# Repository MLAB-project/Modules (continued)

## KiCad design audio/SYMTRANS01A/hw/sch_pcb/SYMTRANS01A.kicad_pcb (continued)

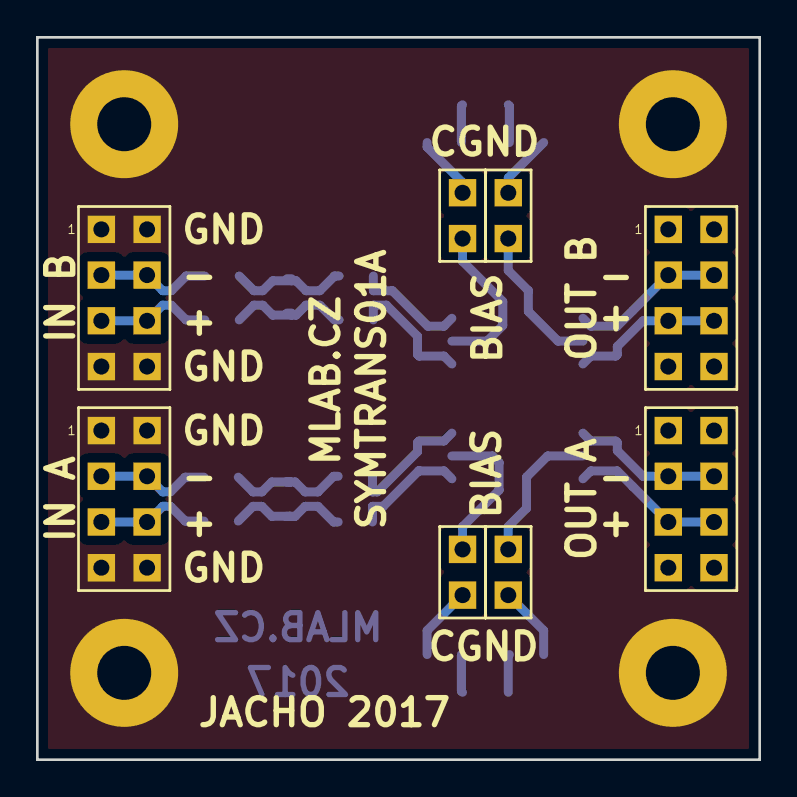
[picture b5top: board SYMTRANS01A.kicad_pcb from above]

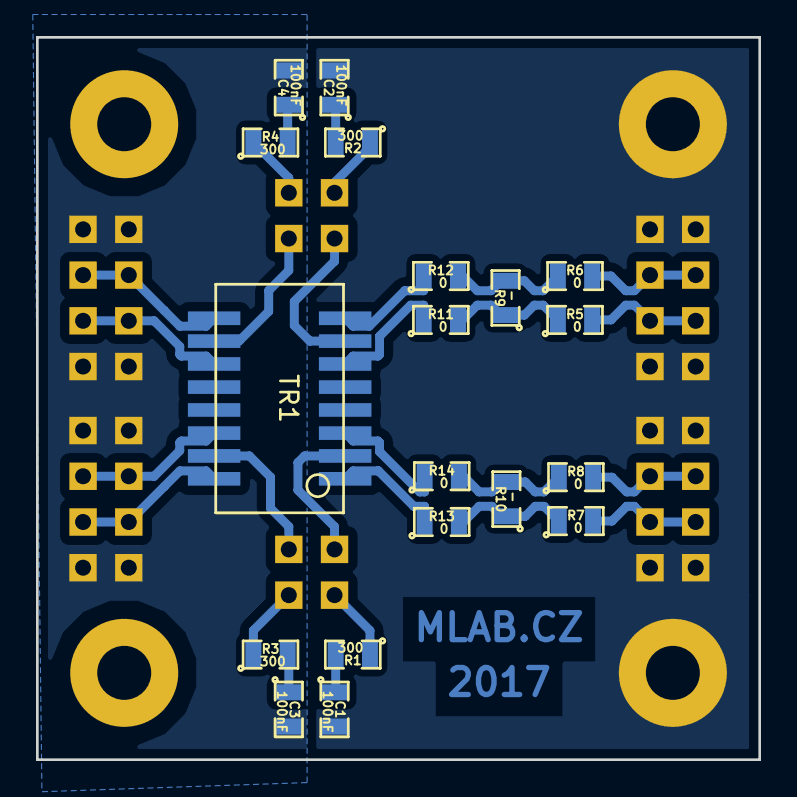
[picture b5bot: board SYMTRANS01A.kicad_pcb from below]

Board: 2 copper layers, 40.1 x 40.1 mm, 31 parts (19 on the bottom side), 30 nets.

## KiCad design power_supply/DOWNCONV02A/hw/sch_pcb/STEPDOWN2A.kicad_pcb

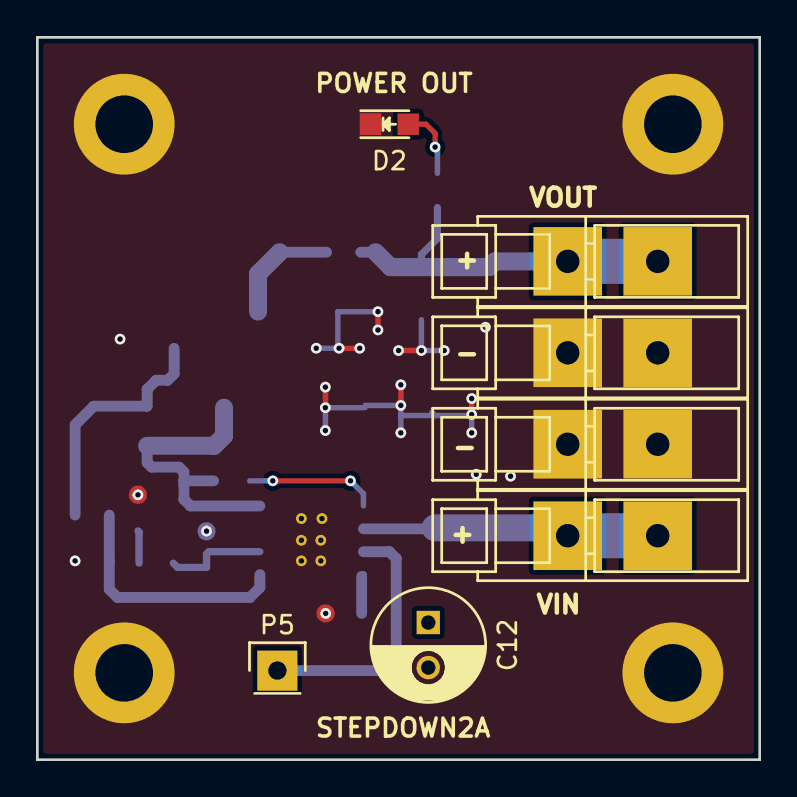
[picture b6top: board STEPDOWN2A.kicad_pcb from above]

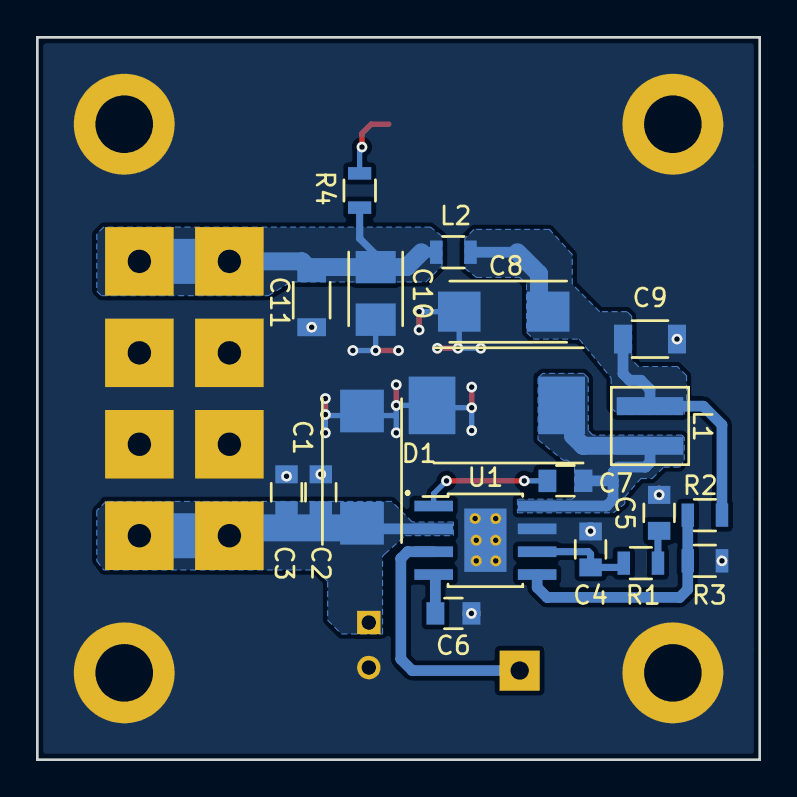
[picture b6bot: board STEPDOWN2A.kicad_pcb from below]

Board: 2 copper layers, 40.1 x 40.1 mm, 30 parts (19 on the bottom side), 12 nets.

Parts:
C1: 22u; TantalC_SizeD_EIA-7343_Reflow
C2: 3u3; C_0805
C3: 1u; C_0805
C4: 18pF; C_0805
C5: 680pF; C_0805
C6: 8n2; C_0805
C7: 100n; C_0805
C8: 22u; TantalC_SizeC_EIA-6032_Reflow
C9, C11: 1u5; C_1206
C10: 22u; TantalC_SizeB_EIA-3528_Reflow
C12: 47u; C_Radial_D6.3_L11.2_P2.5
D1: D_Schottky; DO-214AB
D2: POWER OUT; LED_0805
J1, J2, J3, J4: CONN1_1; WAGO256
L1: 4.7uH; Inductor_XAL4030-472MEB
L2: 240nH; R_0805
P1, P2, P3, P4: _NC; MountingHole_3.2mm_M3_DIN965_Pad
P5: CONN_01X01; Pin_Header_Straight_1x01
R1: 35k7; R_0805
R2: 10k2; R_0805
R3: 1k93; R_0805
R4: 1k2; R_0805
U1: TPS54332; 8-PowerSOIC_Pitch1.27mm

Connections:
+5V: C10.1, C11.1, J3.1, L2.2, R4.1
+12V: C1.1, C2.1, C3.1, C12.1, J1.1, U1.2
/ENABLE: P5.1, U1.3
GND: C1.2, C2.2, C3.2, C4.2, C5.2, C6.2, C8.2, C9.2, C10.2, C11.2, C12.2, D1.2, D2.1, J2.1, J4.1, P1.1, P2.1, P3.1, P4.1, R3.2, U1.7, U1.9
unnamed: C4.1, R1.1, U1.6
unnamed: C5.1, R1.2
unnamed: C6.1, U1.4
unnamed: C7.1, D1.1, L1.1, U1.8
unnamed: C7.2, U1.1
unnamed: C8.1, C9.1, L1.2, L2.1, R2.1
unnamed: D2.2, R4.2
unnamed: R2.2, R3.1, U1.5

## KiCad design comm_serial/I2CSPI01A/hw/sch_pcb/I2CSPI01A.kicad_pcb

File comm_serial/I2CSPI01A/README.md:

[Czech](./README.cs.md)
<!--- module --->
# I2CSPI01A
<!--- Emodule --->

<!--- subtitle --->I2C to SPI bridge<!--- Esubtitle --->

<!--- description --->Allows connection of SPI devices to I2C bus. The module is capable co handle up to four SPI slaves. Not used chip-select pins can be used as GPIO pins.<!--- Edescription --->

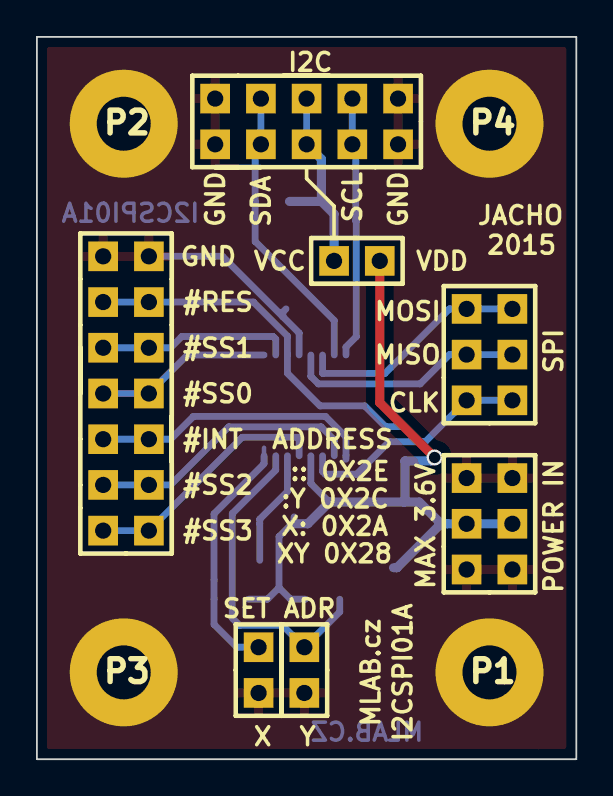
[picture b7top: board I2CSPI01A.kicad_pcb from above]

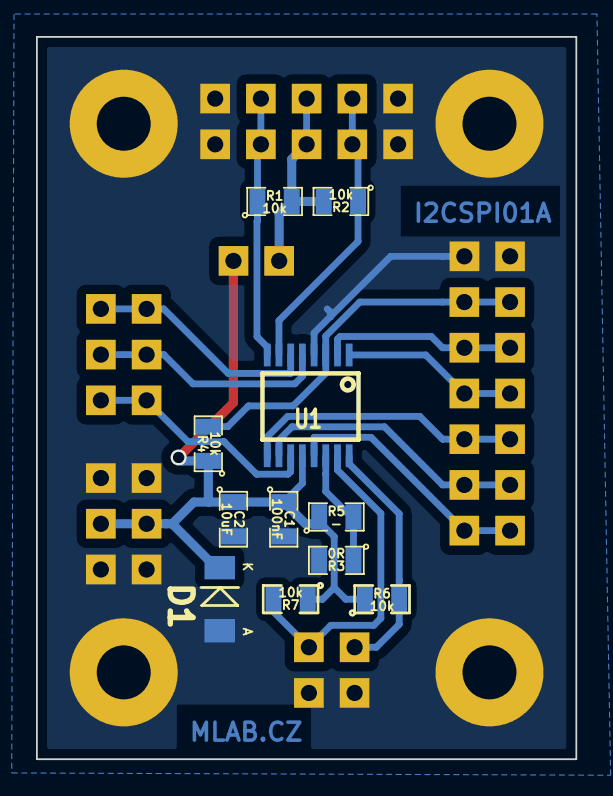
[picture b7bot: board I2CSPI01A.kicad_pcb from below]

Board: 2 copper layers, 30.0 x 40.1 mm, 22 parts (11 on the bottom side), 17 nets.

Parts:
C1: 100nF; SMD-0805
C2: 10uF; SMD-0805
D1: BZV55C-3,6V; Diode-MiniMELF_Standard
J1, J4: JUMP_3X2; Pin_Header_Straight_2x03
J2: JUMP_5X2; Pin_Header_Straight_2x05
J3: JUMP_7X2; Pin_Header_Straight_2x07
J5, J6, J7: CONN_2; Pin_Header_Straight_1x02
P1, P2, P3, P4: _; MountingHole_3mm
R1, R2, R4, R6, R7: 10k; SMD-0805
R3: 0R; SMD-0805
R5: -; SMD-0805
U1: SC18IS602B; TSSOP-16

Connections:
/#INT: J3.3, J3.12, U1.9
/#RES: J3.6, J3.9, R4.2, U1.3
/#SS0: J3.4, J3.11, U1.1
/#SS1: J3.5, J3.10, U1.2
/#SS2: J3.2, J3.13, U1.10
/#SS3: J3.1, J3.14, U1.13
/A0: R3.1, R5.2, U1.14
/A1: J7.2, R7.2, U1.15
/A2: J6.1, R6.2, U1.16
/MISO: J1.2, J1.5, U1.5
/MOSI: J1.3, J1.4, U1.6
/SCL: J2.2, J2.9, R1.1, U1.8
/SDA: J2.4, J2.7, R2.1, U1.7
/SPICLK: J1.1, J1.6, U1.11
GND: C1.2, C2.2, D1.1, J2.1, J2.5, J2.6, J2.10, J3.7, J3.8, J4.1, J4.3, J4.4, J4.6, J6.2, J7.1, P1.1, P2.1, P3.1, P4.1, R3.2, U1.4
unnamed: J2.3, J2.8, J5.1, R1.2, R2.2
VDD: C1.1, C2.1, D1.2, J4.2, J4.5, J5.2, R4.1, R5.1, R6.1, R7.1, U1.12

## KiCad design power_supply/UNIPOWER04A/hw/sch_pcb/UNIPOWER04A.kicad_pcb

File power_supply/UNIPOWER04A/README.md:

[Czech](./README.cs.md)
<!--- module --->
# UNIPOWER04A
<!--- Emodule --->

<!--- subtitle --->UNIPOWER04A <!--- Esubtitle --->

<!--- description ---> Universal 10x 1A power supply module 5V or 12V.<!--- Edescription --->

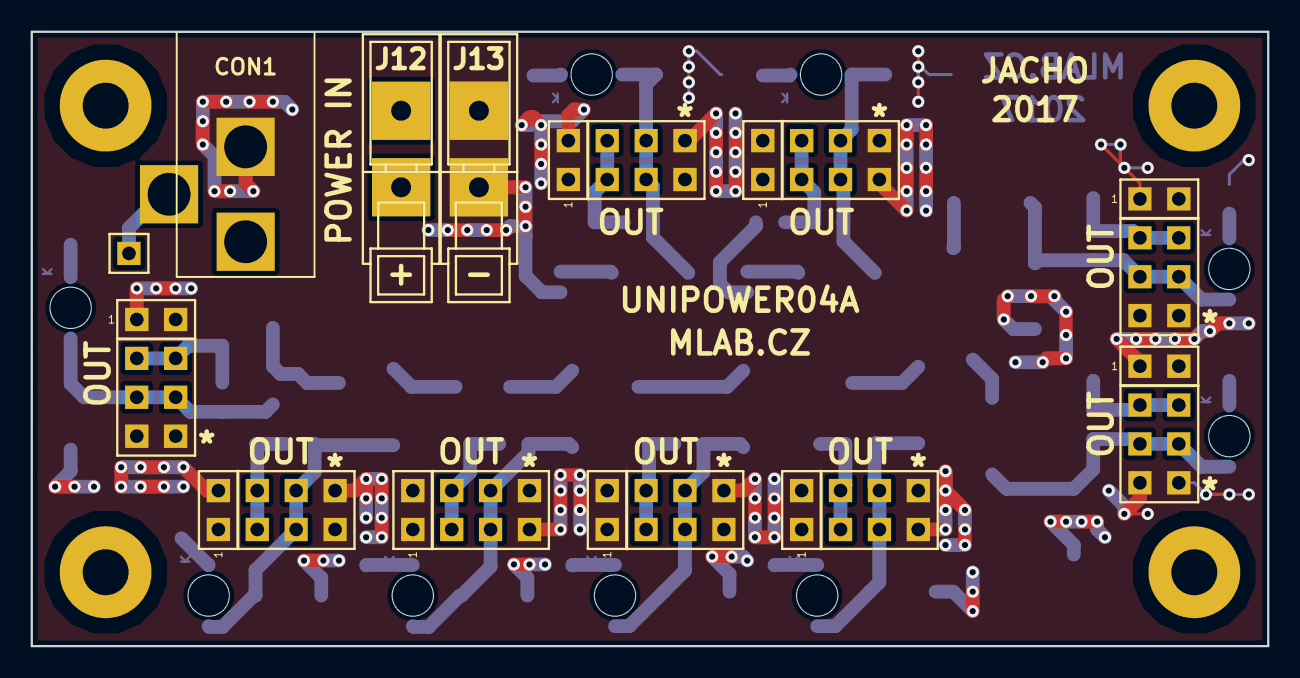
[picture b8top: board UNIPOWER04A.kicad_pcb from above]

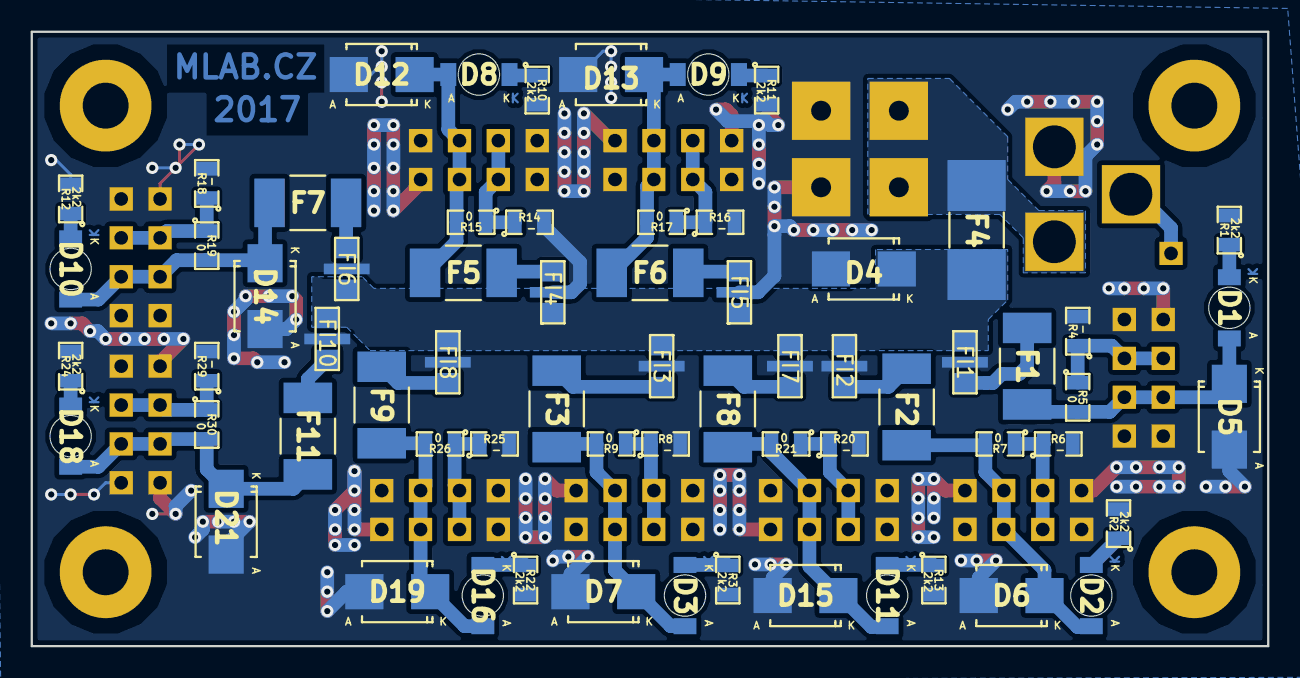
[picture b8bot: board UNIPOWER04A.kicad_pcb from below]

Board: 2 copper layers, 80.8 x 40.1 mm, 82 parts (65 on the bottom side), 40 nets.

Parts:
CON1: JACK_DC2.1; DC2,1MM
D1, D2, D3, D8, D9, D10, D11, D16, D18: RED; LED_1206
D4, D5, D6, D7, D12, D13, D14, D15, D19, D21: SMBJ15A-E3/52; SMB_Standard
F1, F2, F3, F5, F6, F7, F8, F9, F11: 1,1A; 2410
F4: 10A; Drzak_2410
FI1, FI2, FI3, FI4, FI5, FI6, FI7, FI8, FI10: NFM21PC105; FIR1
J1: CONN1_1; Straight_1x01
J2, J3, J4, J5, J6, J7, J8, J9, J11: JUMP_4X2; Straight_2x04
J12, J13: CONN1_1; WAGO256
P1, P2, P3, P4: _; MountingHole_3mm
R1, R2, R3, R10, R11, R12, R13, R22, R24: 2k2; SMD-0805
R4, R6, R8, R14, R16, R18, R20, R25, R29: -; SMD-0805
R5, R7, R9, R15, R17, R19, R21, R26, R30: 0; SMD-0805

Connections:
GND: CON1.2, D4.2, D5.2, D6.2, D7.2, D12.2, D13.2, D14.2, D15.2, D19.2, D21.2, FI1.2, FI2.2, FI3.2, FI4.2, FI5.2, FI6.2, FI7.2, FI8.2, FI10.2, J2.1, J2.2, J2.7, J2.8, J3.1, J3.2, J3.7, J3.8, J4.1, J4.2, J4.7, J4.8, J5.1, J5.2, J5.7, J5.8, J6.1, J6.2, J6.7, J6.8, J7.1, J7.2, J7.7, J7.8, J8.1, J8.2, J8.7, J8.8, J9.1, J9.2, J9.7, J9.8, J11.1, J11.2, J11.7, J11.8, J13.1, R1.2, R2.2, R3.2, R4.2, R6.2, R8.2, R10.2, R11.2, R12.2, R13.2, R14.2, R16.2, R18.2, R20.2, R22.2, R24.2, R25.2, R29.2
unnamed: CON1.1, F4.1, J12.1
unnamed: CON1.3, J1.1
unnamed: D1.1, R1.1
unnamed: D1.2, D5.1, F1.2, J2.5, J2.6, R5.2
unnamed: D2.1, R2.1
unnamed: D2.2, D6.1, F2.2, J3.5, J3.6, R7.2
unnamed: D3.1, R3.1
unnamed: D3.2, D7.1, F3.2, J4.5, J4.6, R9.2
unnamed: D8.1, R10.1
unnamed: D9.1, R11.1
unnamed: D10.1, R12.1
unnamed: D10.2, D14.1, F7.2, J7.5, J7.6, R19.2
unnamed: D11.1, R13.1
unnamed: D11.2, D15.1, F8.2, J8.5, J8.6, R21.2
unnamed: D8.2, D12.1, F5.2, J5.5, J5.6, R15.2
unnamed: D9.2, D13.1, F6.2, J6.5, J6.6, R17.2
unnamed: D16.1, R22.1
unnamed: D16.2, D19.1, F9.2, J9.5, J9.6, R26.2
unnamed: D18.1, R24.1
unnamed: D18.2, D21.1, F11.2, J11.5, J11.6, R30.2
unnamed: F1.1, FI1.3
unnamed: F2.1, FI2.3
unnamed: F3.1, FI3.3
unnamed: F5.1, FI4.3
unnamed: F6.1, FI5.3
unnamed: F7.1, FI6.3
unnamed: F8.1, FI7.3
unnamed: F9.1, FI8.3
unnamed: F11.1, FI10.3
unnamed: J2.3, J2.4, R4.1, R5.1
unnamed: J3.3, J3.4, R6.1, R7.1
unnamed: J4.3, J4.4, R8.1, R9.1
unnamed: J5.3, J5.4, R14.1, R15.1
unnamed: J6.3, J6.4, R16.1, R17.1
unnamed: J7.3, J7.4, R18.1, R19.1
unnamed: J8.3, J8.4, R20.1, R21.1
unnamed: J9.3, J9.4, R25.1, R26.1
unnamed: J11.3, J11.4, R29.1, R30.1
VCC: D4.1, F4.2, FI1.1, FI2.1, FI3.1, FI4.1, FI5.1, FI6.1, FI7.1, FI8.1, FI10.1

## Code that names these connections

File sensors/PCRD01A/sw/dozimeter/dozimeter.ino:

/* PCRD */

/*
 * SD card attached to SPI bus as follows:
 ** SDcard01B/CMD      MOSI - pin PB3
 ** SDcard01B/DATA0    MISO - pin PB4
 ** SDcard01B/CLK      CLK  - pin PB5
 ** SDcard01B/CD/DATA3 CS   - pin PD4
*/

#include <SD.h>

const String filename = "log.csv";  // filename for logfile

const int detector=3; // PD3
const int eint=2;     // PD2
const int LED1=8;     // PB0
const int LED2=9;     // PB1
const int LED3=10;    // PB2
const int LED4=7;     // PD7
const int chipSelect = 4;     // CS is PD4

const int CHANNELS=64;  // Number of channels

unsigned int channel[CHANNELS];    // recordig buffer
int interval=0;               // seconds counter
boolean rise=false;           // flag fo recording time
char inChar;                  // input character from GPS
String dataString = "";       // concantenated string with NMEA messages and measured values
int coll = 0;                 // collons counter in NMEA messages
unsigned int i = 0;           // measurements counter


// function for reading $GPRMC NMEA message
void ReadGPRMC()
{
  // $GPRMC,091451.00,A,4915.64143,N,01441.50397,E,0.053,,090215,,,A*74
  coll = 0;
  while(1)    // wait for $GPRMC
  {
    // get incoming byte:
    while (!Serial.available());
    if (Serial.read() != '$') continue;
    while (!Serial.available());
    if (Serial.read() != 'G') continue;
    while (!Serial.available());
    if (Serial.read() != 'P') continue;
    while (!Serial.available());
    if (Serial.read() != 'R') continue;
    while (!Serial.available());
    if (Serial.read() != 'M') continue;
    while (!Serial.available());
    if (Serial.read() != 'C') continue;
    while (!Serial.available());
    if (Serial.read() != ',') continue;
    break;
  }  
  do
  {
    while (!Serial.available());
    inChar = (char)Serial.read();
    if (inChar == ',') coll++;
    dataString += inChar;
  }
  while (coll < 9);  // read only 9 coma separated values
}

// function for reading $GPGGA NMEA message
void ReadGPGGA()
{
  // $GPGGA,091451.00,4915.64143,N,01441.50397,E,1,09,0.90,443.2,M,44.0,M,,*50
  coll = 0;
  while(1)  // wait for $GPGGA
  {
    while (!Serial.available());
    if (Serial.read() != '$') continue;
    while (!Serial.available());
    if (Serial.read() != 'G') continue;
    while (!Serial.available());
    if (Serial.read() != 'P') continue;
    while (!Serial.available());
    if (Serial.read() != 'G') continue;
    while (!Serial.available());
    if (Serial.read() != 'G') continue;
    while (!Serial.available());
    if (Serial.read() != 'A') continue;
    while (!Serial.available());
    if (Serial.read() != ',') continue;
    break;
  }  
  do
  {
    while (!Serial.available());
    inChar = (char)Serial.read();
    if (inChar == ',') coll++;
    if (coll > 4) dataString += inChar;  // skip first 5 coma separated values
  }
  while (coll < 12); // read only 7 coma separated values
}

void isr()        // interrupt service routine driven from 1PPS from GPS
{
  if (++interval == 10) // 10 seconds
  {
    rise=true;
    interval = 0;
  }

}

void record()
{
  for (int c=16; c<CHANNELS; c++)
  {
    if (channel[c]>0)
    {
      digitalWrite(LED4, HIGH);   // LED 16-64
      break;      
    }
  }

  for (int c=9; c<17; c++)
  {
    if (channel[c]>0)
    {
      digitalWrite(LED3, HIGH);   // LED 9-16
      break;      
    }
  }

  for (int c=5; c<9; c++)
  {
    if (channel[c]>0)
    {
      digitalWrite(LED2, HIGH);   // LED 5-8
      break;      
    }
  }

  for (int c=0; c<5; c++)
  {
    if (channel[c]>0)
    {
      digitalWrite(LED1, HIGH);   // LED 0-4
      break;      
    }
  }
     
  dataString = "";        // make a string for assembling the data to log
  ReadGPRMC();            // read NMEA sentences from GPS
  ReadGPGGA();
  // make a string for assembling the data to log:
  dataString += String(i++);
  //dataString += ","; 
  //Serial.print(dataString);

  for (int n=0; n<CHANNELS; n++)
  {
    dataString += ","; 
    dataString += String(channel[n]);
    //Serial.print(channel[n]);
    //Serial.print(',');
  }
  //Serial.println();
  
  // open the file. note that only one file can be open at a time,
  // so you have to close this one before opening another.
  char fileNameCharArray[filename.length()];
  filename.toCharArray(fileNameCharArray, filename.length());
  File dataFile = SD.open(fileNameCharArray, FILE_WRITE);

  // if the file is available, write to it:
  if (dataFile) 
  {
    dataFile.println(dataString);
    dataFile.close();
    // print to the serial port too:
    Serial.println(dataString);
  }  
  // if the file isn't open, pop up an error:
  else {
    Serial.println("error opening datalog.CSV");
  } 

  for (int n=0; n<CHANNELS; n++) // clear recording buffer
  {
    channel[n]=0;
  }  

  digitalWrite(LED1, LOW);   // LED OFF
  digitalWrite(LED2, LOW);   // LED OFF
  digitalWrite(LED3, LOW);   // LED OFF
  digitalWrite(LED4, LOW);   // LED OFF

}

void setup() 
{
 // Open serial communications and wait for port to open:
  Serial.begin(9600);
  while (!Serial) {;}
  Serial.println("cvak");

  pinMode(detector, INPUT);
  pinMode(eint, INPUT);
  pinMode(LED1, OUTPUT);
  pinMode(LED2, OUTPUT);
  pinMode(LED3, OUTPUT);
  pinMode(LED4, OUTPUT);


  Serial.print("Initializing SD card...");  // inserting a SD Card always reset the processor and call setup
  // make sure that the default chip select pin is set to
  // output, even if you don't use it:
  //pinMode(10, OUTPUT); // PB2
  //pinMode(LED, OUTPUT);     

  // see if the card is present and can be initialized:
  if (!SD.begin(chipSelect)) 
  {
    Serial.println("Card failed, or not present");
    // don't do anything more:
    return;
  }
  Serial.println("card initialized.");

  noInterrupts();          // disable all interrupts
  attachInterrupt(0, isr, RISING);  // initialise interrupt from rising edge of 1PPS

  for (int n=0; n<CHANNELS; n++) // clear recoding buffer
  {
    channel[n]=0; 
  }

  interrupts();             // enable all interrupts
  
  Serial.println("Hmmm");
}

void loop() 
{
  while (true)
  {
    unsigned int duration=0;               // pulse duration counter
  
    while (!digitalRead(detector))  // waiting for pulse
    {
      if (rise) break;
    }
    while (digitalRead(detector)) 
    {
      if (rise) break;
      if (duration < (CHANNELS-1)) duration++;
    }
    if (rise)  // recording time is now
    {
        record();  // make record
        rise = false;
        continue;  // skip this interrupted impuls
    }
    if (channel[duration] < 65535) channel[duration]++;  /// record duration in apropriate channel
  }
}

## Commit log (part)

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2022-02-16 [MLABweb] Documentation edits; TRIMQUAD01A
2022-02-16 [MLABweb] Documentation edits; LEDbar01A
2022-02-16 [MLABweb] Documentation edits; SDcard01A
2022-02-16 [MLABweb] Documentation edits; PIC16F87xTQ4401A
2022-02-16 [MLABweb] Documentation edits; PICICD01B
2022-02-16 [MLABweb] Documentation edits; Galileo
2022-02-16 [MLABweb] Documentation edits; ATmega8DIL01A
2022-02-16 [MLABweb] Documentation edits; AVRUSB01A
2022-02-16 [MLABweb] Documentation edits; ATmegaTQ10001A
2022-02-16 [MLABweb] Documentation edits; RFM02SMD01A
2022-02-16 [MLABweb] Documentation edits; BP01A
2022-02-16 [MLABweb] Documentation edits; PCRD01A
2022-02-16 [MLABweb] Documentation edits; S3AN01B
2022-02-16 [MLABweb] Documentation edits; LDD01A
2022-02-16 [MLABweb] Documentation edits; SMA2SATA01A
2022-02-16 [MLABweb] Documentation edits; HBRIDGE02A
2022-02-16 [MLABweb] Documentation edits; HBRIDGE01B
2022-02-16 [MLABweb] Documentation edits; MPC17511HB01A
2022-02-16 [MLABweb] Documentation edits; S3AN01A
2022-02-16 [MLABweb] Documentation edits; OZquad01A
2022-02-16 [MLABweb] Documentation edits; POWERDAC01A
2022-02-16 [MLABweb] Documentation edits; MBA81001A
2022-02-16 [MLABweb] Documentation edits; NFET2X01A
2022-02-16 [MLABweb] Documentation edits; PWMLED01A
2022-02-16 [MLABweb] Documentation edits; CLKGEN01A
2022-02-16 [MLABweb] Documentation edits; USB232R01A
2022-02-16 [MLABweb] Documentation edits; I2CHUB01B
2022-02-16 [MLABweb] Documentation edits; ETH01A
2022-02-16 [MLABweb] Documentation edits; SUPERCAP01A
2022-02-16 [MLABweb] Documentation edits; LION2CELL01C
2022-02-16 [MLABweb] Documentation edits; BATPOWER02A
2022-02-16 [MLABweb] Documentation edits; GPS02A
2022-02-17 [MLABweb] Documentation edits; CLKHUB01A
2022-02-17 Module moved to separate repository https://github.com/mlab-modules/ADCoctoSPI01
2022-02-17 Update submodule.
2022-02-18 Remove redundant files to submodules from the repository.
2022-03-08 TTLLVDS01A moved to separate submodule. https://github.com/mlab-modules/TTLLVDS01
2022-04-03 Add links to datasheets.
2022-04-03 Adding submodule STEPUPDC01A
2022-04-05 Adding USBI2C01A as submodule.
2022-04-05 Adding I2CHUB02 as submodule.
2022-08-14 Moving VCAI2C01 to separate repository. https://github.com/mlab-modules/VCAI2C01
2022-08-14 adding submodules of separate repositories.
2023-02-07 Removing ACOMP01A module. Will be designed from ground in the new repository.
2023-04-01 Removing ADC modules splitted to separate repositories.
2023-05-08 Removing ALBASE modules splitted to separate repositories.
2023-05-08 update split script
2023-05-08 Removing ALBASE1609 modules splitted to separate repositories.
2023-05-08 Removing ALBASE1608 modules splitted to separate repositories.
2023-05-08 Removing ALBASE1505 modules splitted to separate repositories.
2023-05-08 Removing ALBASE1241 modules splitted to separate repositories.
2023-05-08 Removing UNIPOWER02A modules splitted to separate repositories.
2023-05-09 Removing BATPOWER04C modules splitted to separate repositories.
2023-05-09 BATPOWER04 to submodule
2023-05-24 update submodule
2023-05-25 update submodle
2023-05-25 Removing CCP2019V01A modules splitted to separate repositories.
2023-05-25 Removing HCS01A modules splitted to separate repositories.
2023-05-25 Removing PIND01A modules splitted to separate repositories.
2023-05-25 Removing RGBC01A modules splitted to separate repositories.
2023-05-25 Removing RPS01A modules splitted to separate repositories.
2023-05-25 Removing SHT31V01A modules splitted to separate repositories.
2023-05-25 Removing THERMOPHILE01A modules splitted to separate repositories.
2023-05-25 Removing TTLPROBE02A modules splitted to separate repositories.
2023-05-25 Removing I2CDIFF01B modules splitted to separate repositories.
2023-05-25 Removing TTLPECL01A modules splitted to separate repositories.
2023-05-25 Removing HUM01A modules splitted to separate repositories.
2023-05-25 Removing IRFEE01A modules splitted to separate repositories.
2023-05-25 Removing ISL03A modules splitted to separate repositories.
2023-05-25 Removing IUC01A modules splitted to separate repositories.
2023-05-25 Removing LIGHTNING01A modules splitted to separate repositories.
2023-05-25 Removing MAG01A modules splitted to separate repositories.
2023-05-25 Removing Pulse_catch01A modules splitted to separate repositories.
2023-06-20 Removing ADCmonoPPI01A modules splitted to separate repositories.
2023-06-20 Removing ADCmonoSPI01B modules splitted to separate repositories.
2023-06-20 Removing ISPLSI1016A modules splitted to separate repositories.
2023-06-20 Removing S3AN01B modules splitted to separate repositories.
2023-06-20 Removing IRDA01A modules splitted to separate repositories.
2023-06-20 Removing TXIR01B modules splitted to separate repositories.
2023-06-20 Removing STM32F30xRx01A modules splitted to separate repositories.
2023-06-20 Removing ATmega801A modules splitted to separate repositories.
2023-06-20 Removing ATmega8DIL01A modules splitted to separate repositories.
2023-06-20 Removing ATmegaTQ3201A modules splitted to separate repositories.
2023-06-20 Removing ATmegaTQ6401A modules splitted to separate repositories.
2023-06-20 Removing ATprogISPUSB02A modules splitted to separate repositories.
2023-06-20 Removing ATtinySO801B modules splitted to separate repositories.
2023-06-20 Removing PICPROGUSB02A modules splitted to separate repositories.
2023-06-20 Removing PIC16F84SO1801A modules splitted to separate repositories.
2023-06-20 Removing PIC16F87xTQ4401B modules splitted to separate repositories.
2023-06-20 Removing PICPGR301A modules splitted to separate repositories.
2023-06-20 Removing PIC16F87xSO2801A modules splitted to separate repositories.
2023-06-20 Removing PIC16F87xDIL2801A modules splitted to separate repositories.
2023-06-20 Removing PIC18F2550v01A modules splitted to separate repositories.
2023-06-20 Removing PIC16F87xTQ4401A modules splitted to separate repositories.
2023-06-20 Removing RFdetect01A modules splitted to separate repositories.
2023-06-20 Removing BLE01A modules splitted to separate repositories.
2023-06-20 Removing RFM02SMD01A modules splitted to separate repositories.
2023-06-20 Removing TXsaw433MHz01A modules splitted to separate repositories.
2023-06-20 Removing GSM01A modules splitted to separate repositories.
2023-06-20 Removing RFM01SMD01A modules splitted to separate repositories.
2023-06-20 Removing BP01A modules splitted to separate repositories.
2023-06-20 Removing RFMIX01A modules splitted to separate repositories.
2023-06-20 Removing FORX01A modules splitted to separate repositories.
2023-06-20 Removing GSM01B modules splitted to separate repositories.
2023-06-20 Removing GP201A modules splitted to separate repositories.
2023-06-20 Removing ADCaudio01B modules splitted to separate repositories.
2023-06-20 Removing SYMTRANS01A modules splitted to separate repositories.
2023-06-20 Removing POWERDAC01A modules splitted to separate repositories.
2023-06-20 Removing AD1881A01A modules splitted to separate repositories.
2023-06-20 Removing CLKDIV01A modules splitted to separate repositories.
2023-06-20 Removing RTC03A modules splitted to separate repositories.
2023-06-20 Removing RTC01A modules splitted to separate repositories.
2023-06-20 Removing CLKGEN01B modules splitted to separate repositories.
2023-06-20 Removing CLKHUB02A modules splitted to separate repositories.
2023-06-20 Removing I2CHUB02B modules splitted to separate repositories.
2023-06-20 Removing SERVOHUB01A modules splitted to separate repositories.
2023-06-20 Removing I2CIO01A modules splitted to separate repositories.
2023-06-20 Removing I2CHUB01B modules splitted to separate repositories.
2023-06-20 Removing USBIO01A modules splitted to separate repositories.
2023-06-20 Removing TTLRS48501A modules splitted to separate repositories.
2023-06-20 Removing USBI2S01A modules splitted to separate repositories.
2023-06-20 Removing USB4xUART01A modules splitted to separate repositories.
2023-06-20 Removing ETH02A modules splitted to separate repositories.
2023-06-20 Removing TBPCIE01A modules splitted to separate repositories.
2023-06-20 Removing LED01A modules splitted to separate repositories.
2023-06-20 Removing DIP8SW01A modules splitted to separate repositories.
2023-06-20 Removing LCD2L4P01A modules splitted to separate repositories.
2023-06-20 Removing LEDbar01A modules splitted to separate repositories.
2023-06-20 Removing LED7SEG01A modules splitted to separate repositories.
2023-06-20 Removing nanoterm01A modules splitted to separate repositories.
2023-06-20 Removing SW01A modules splitted to separate repositories.
2023-06-20 Removing TOUCHBOARD01A modules splitted to separate repositories.
2023-06-20 Removing TRIM01A modules splitted to separate repositories.
2023-06-20 Removing AWSCREEN02A modules splitted to separate repositories.
2023-06-20 Removing BOXHOLDER01A modules splitted to separate repositories.
2023-06-20 Removing ISLHOLDER01A modules splitted to separate repositories.
2023-06-20 Removing RAINGUAGE01A modules splitted to separate repositories.
2023-06-20 Removing WINDGAUGE02A modules splitted to separate repositories.
2023-06-20 Removing EEPROM01A modules splitted to separate repositories.
2023-06-20 Removing SDcard01A modules splitted to separate repositories.
2023-06-20 Removing AXISCONTROL01A modules splitted to separate repositories.
2023-06-20 Removing DRV8835HB01B modules splitted to separate repositories.
2023-06-20 Removing HBRIDGE01B modules splitted to separate repositories.
2023-06-20 Removing HBRIDGE03A modules splitted to separate repositories.
2023-06-20 Removing HBSTEP01B modules splitted to separate repositories.
2023-06-20 Removing HB1FET01A modules splitted to separate repositories.
2023-06-20 Removing HT675101A modules splitted to separate repositories.
2023-06-20 Removing MPC17529HB01A modules splitted to separate repositories.
2023-06-20 Removing 3PHBRIDGE01A modules splitted to separate repositories.
2023-06-20 Removing OZDUAL02A modules splitted to separate repositories.
2023-06-20 Removing OZDUAL02B modules splitted to separate repositories.
2023-06-20 Removing OZDUAL03B modules splitted to separate repositories.
2023-06-20 Removing OZquad01A modules splitted to separate repositories.
2023-06-20 Removing ATXPOWER01A modules splitted to separate repositories.
2023-06-20 Removing BATPOWER02A modules splitted to separate repositories.
2023-06-20 Removing BATPOWER05A modules splitted to separate repositories.
2023-06-20 Removing DOWNCONV02A modules splitted to separate repositories.
2023-06-20 Removing CHPUMP01A modules splitted to separate repositories.
2023-06-20 Removing LM108601A modules splitted to separate repositories.
2023-06-20 Removing SOLAR01A modules splitted to separate repositories.
2023-06-20 Removing SUPERCAP01B modules splitted to separate repositories.
2023-06-20 Removing SYMPOWER02A modules splitted to separate repositories.
2023-06-20 Removing TPS63036V01A modules splitted to separate repositories.
2023-06-20 Removing UNIPOWER04A modules splitted to separate repositories.
2023-06-20 Removing UNIPOWER06A modules splitted to separate repositories.
2023-06-20 Removing UNIPOWER08A modules splitted to separate repositories.
2023-06-20 Removing COILSW01A modules splitted to separate repositories.
2023-06-20 Removing DIG4SW01A modules splitted to separate repositories.
2023-06-20 Removing NFET2X01A modules splitted to separate repositories.
2023-06-20 Removing NFET4X01B modules splitted to separate repositories.
2023-06-20 Removing PWMLED01B modules splitted to separate repositories.
2023-06-20 Removing REL1SW01A modules splitted to separate repositories.
2023-06-20 Removing TRIACSHARP02A modules splitted to separate repositories.
2023-06-20 Removing FMC2DIFF01A modules splitted to separate repositories.
2023-06-20 Removing RJ12V01A modules splitted to separate repositories.
2023-06-20 Removing RJ45V01A modules splitted to separate repositories.
2023-06-20 Removing UNIATMEGA8TQFP01A modules splitted to separate repositories.
2023-06-20 Removing UNISERIAL01A modules splitted to separate repositories.
